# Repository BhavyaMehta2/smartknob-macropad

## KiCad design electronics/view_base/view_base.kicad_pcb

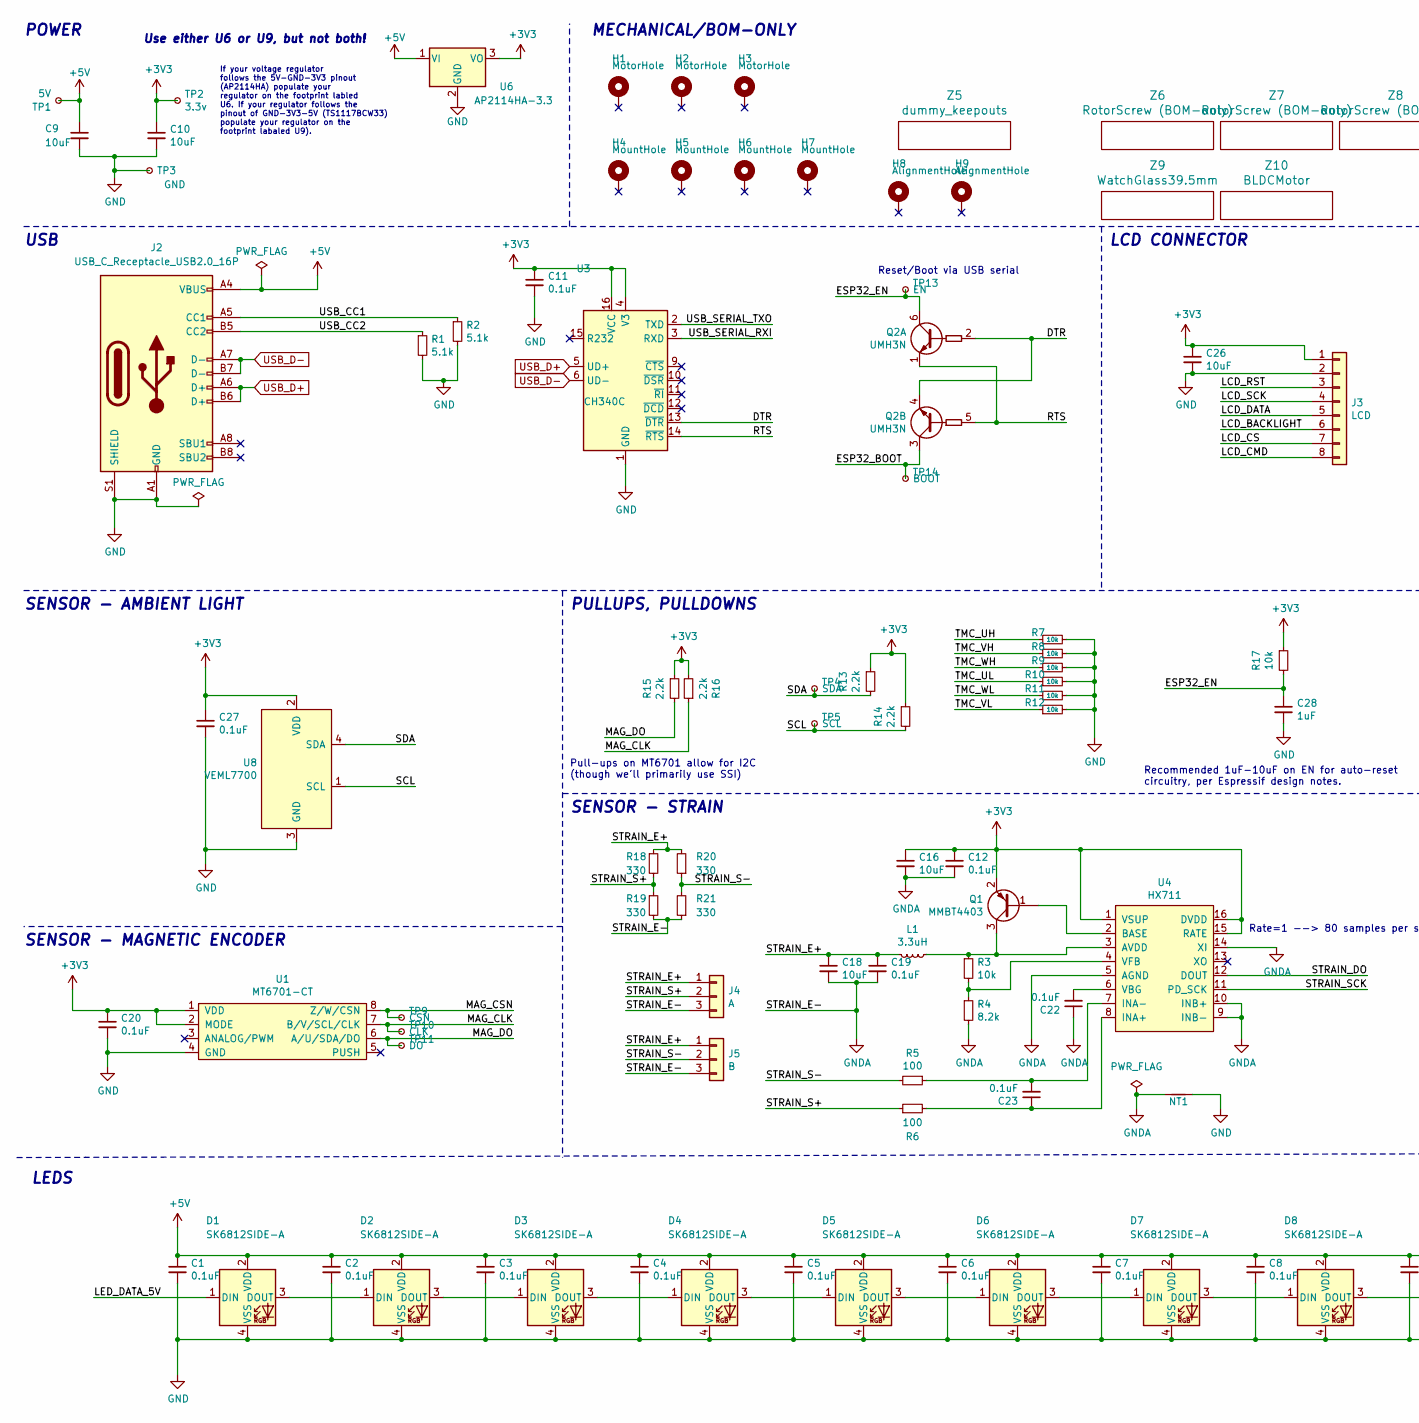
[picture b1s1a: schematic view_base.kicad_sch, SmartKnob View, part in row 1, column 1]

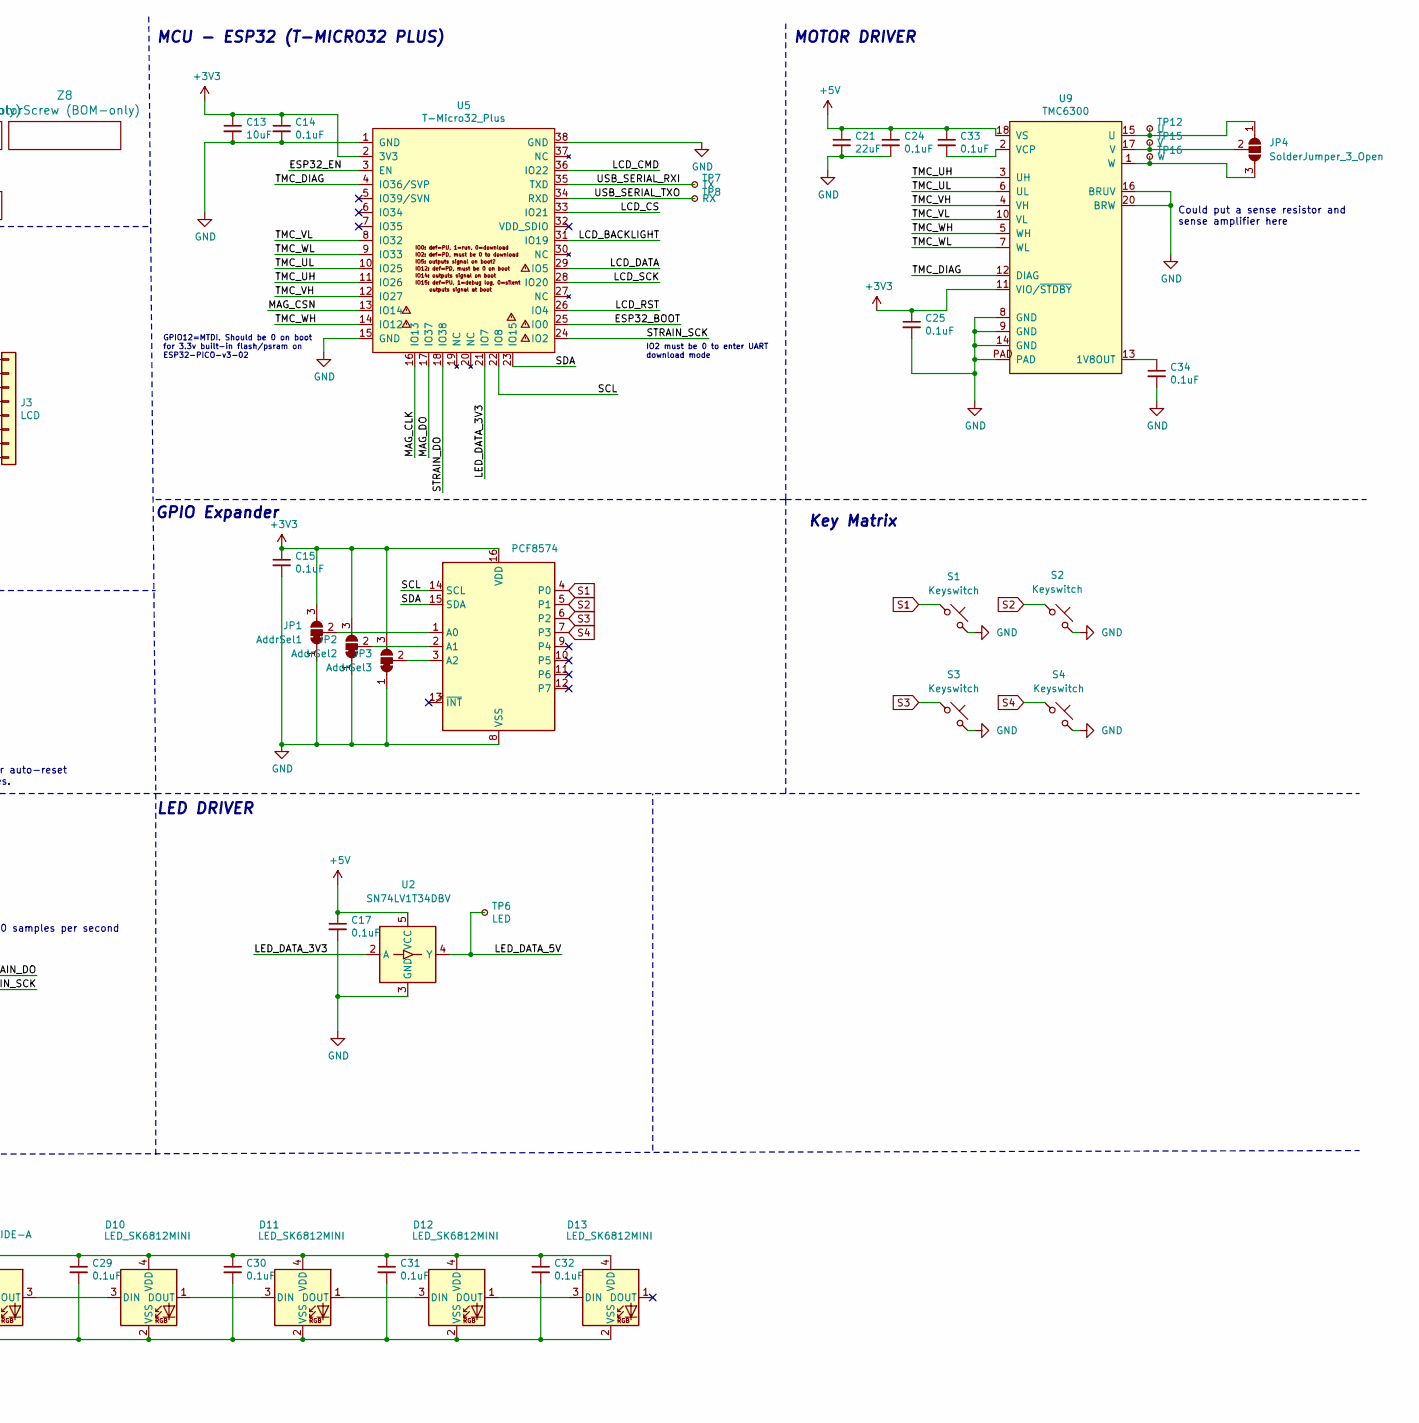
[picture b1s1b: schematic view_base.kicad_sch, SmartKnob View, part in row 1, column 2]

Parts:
C1, C2, C3, C4, C5, C6, C7, C8, C11, C12, C14, C15, C17, C19, C20, C22, C23, C24, C25, C27, C29, C30, C31, C32, C33, C34: 0.1uF; C_0603_1608Metric; LCSC C1591
C9, C10, C13, C16, C18, C26: 10uF; C_0805_2012Metric; LCSC C15850
C21: 22uF; C_0805_2012Metric; LCSC C98190
C28: 1uF; C_0603_1608Metric; Mouser 187-CL10A105KA8NNNC
D1, D2, D3, D4, D5, D6, D7, D8: SK6812SIDE-A; SK6812-SIDE-A; Digikey 1528-4691-ND
D10, D11, D12, D13: LED_SK6812MINI; MX_SK6812MINI-E
H1, H2, H3: MotorHole; MountingHole_M1.6; LCSC C2931389
H4, H5, H6, H7: MountHole; MountingHole_2.2mm_M2_ISO7380_Pad_NonVirtual; LCSC C2911210 or C2911532 (screw), C2961595 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
H8, H9: AlignmentHole; MountingHole_2.2mm_M2_ISO7380_Pad_NonVirtual
J2: USB_C_Receptacle_USB2.0_16P; USB4510_NoPaste
J3: LCD; SolderPads_2mm_8
J4: A; SolderPads_2mm_3_STRAIN
J5: B; SolderPads_2mm_3_STRAIN
JP1: AddrSel1; SolderJumper-3_P1.3mm_Bridged12_Pad1.0x1.5mm_NumberLabels
JP2: AddrSel2; SolderJumper-3_P1.3mm_Bridged12_Pad1.0x1.5mm_NumberLabels
JP3: AddrSel3; SolderJumper-3_P1.3mm_Bridged12_Pad1.0x1.5mm_NumberLabels
JP4: SolderJumper_3_Open; SolderPads_2mm_3
L1: 3.3uH; L_0805_2012Metric; LCSC C307744
NT1: NetTie_2; NetTie-2_SMD_Pad0.5mm
Q1: MMBT4403; SOT-23; LCSC C78864
Q2: UMH3N; SOT-363_SC-70-6; LCSC C62892
R1, R2: 5.1k; R_0603_1608Metric; LCSC C105580
R3, R7, R8, R9, R10, R11, R12, R17: 10k; R_0603_1608Metric; LCSC C98220
R4: 8.2k; R_0603_1608Metric; LCSC C114637
R5, R6: 100; R_0603_1608Metric; LCSC C319953
R13, R14, R15, R16: 2.2k; R_0603_1608Metric; LCSC C4190
R18, R19, R20, R21: 330; R_2512_6332Metric; LCSC C19866
S1, S2, S3, S4: Keyswitch; MX_PCB_1.00u
TP1: 5V; TestPoint_Pad_D2.0mm_ValueSilk
TP2: 3.3v; TestPoint_Pad_D2.0mm_ValueSilk
TP3: GND; TestPoint_Pad_D2.0mm_ValueSilk
TP4: SDA; TestPoint_Pad_D2.0mm_ValueSilk
TP5: SCL; TestPoint_Pad_D2.0mm_ValueSilk
TP6: LED; TestPoint_Pad_D2.0mm_ValueSilk
TP7: TX; TestPoint_Pad_D2.0mm_ValueSilk
TP8: RX; TestPoint_Pad_D2.0mm_ValueSilk
TP9: CSN; TestPoint_Pad_D2.0mm_ValueSilk
TP10: CLK; TestPoint_Pad_D2.0mm_ValueSilk
TP11: DO; TestPoint_Pad_D2.0mm_ValueSilk
TP12: U; TestPoint_Pad_D2.0mm_ValueSilk
TP13: EN; TestPoint_Pad_D2.0mm_ValueSilk
TP14: BOOT; TestPoint_Pad_D2.0mm_ValueSilk
TP15: V; TestPoint_Pad_D2.0mm_ValueSilk
TP16: W; TestPoint_Pad_D2.0mm_ValueSilk
U1: MT6701-CT; SOIC-8_3.9x4.9mm_P1.27mm; LCSC C2856764, or C3003196
U2: SN74LV1T34DBV; SOT-23-5; LCSC C100024
U3: CH340C; SOIC-16_3.9x9.9mm_P1.27mm; LCSC C84681
U4: HX711; SOIC-16_3.9x9.9mm_P1.27mm; LCSC C43656
U5: T-Micro32_Plus; T-Micro32; Digikey N/A
U6: AP2114HA-3.3; SOT-223-3_TabPin2_InGndOut; LCSC C460314
U7: PCF8574; SOP-16_3.9x9.9mm_P1.27mm
U8: VEML7700; VEML7700-TOP; Digikey VEML7700-TT
U9: TMC6300; QFN-20-1EP_3x3mm_P0.4mm_EP1.65x1.65mm_ThermalVias_LargerVia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; Digikey TMC6300-LA-T
Z5: dummy_keepouts; ViewKeepouts3d
Z6, Z7, Z8: RotorScrew (BOM-only); bom_only_no_pin
Z9: WatchGlass39.5mm; bom_only_no_pin
Z10: BLDCMotor; bom_only_no_pin

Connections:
+3V3: C10.1, C11.1, C12.1, C13.1, C14.1, C15.1, C16.1, C20.1, C25.1, C26.1, C27.1, J3.1, JP1.3 (B), JP2.3 (B), JP3.3 (B), Q1.2 (E), R13.1, R14.1, R15.1, R16.2, R17.1, TP2.1, U1.1 (VDD), U1.2 (MODE), U3.4 (V3), U3.16 (VCC), U4.1 (VSUP), U4.15 (RATE), U4.16 (DVDD), U5.2 (3V3), U6.3 (VO), U7.16 (VDD), U8.2 (VDD), U9.11 (VIO/~STDBY)
+5V: C1.1, C2.1, C3.1, C4.1, C5.1, C6.1, C7.1, C8.1, C9.1, C17.1, C21.1, C24.1, C29.1, C30.1, C31.1, C32.1, C33.1, D1.2 (VDD), D2.2 (VDD), D3.2 (VDD), D4.2 (VDD), D5.2 (VDD), D6.2 (VDD), D7.2 (VDD), D8.2 (VDD), D10.4 (VDD), D11.4 (VDD), D12.4 (VDD), D13.4 (VDD), J2.A4 (VBUS), J2.A9 (VBUS), J2.B4 (VBUS), J2.B9 (VBUS), TP1.1, U2.5 (VCC), U6.1 (VI), U9.18 (VS)
/DTR: Q2.2 (B1), Q2.4 (E2), U3.13 (~DTR)
/ESP32_BOOT: Q2.3 (C2), TP14.1, U5.25 (IO0)
/ESP32_EN: C28.1, Q2.6 (C1), R17.2, TP13.1, U5.3 (EN)
/LCD_BACKLIGHT: J3.6, U5.31 (IO19)
/LCD_CMD: J3.8, U5.36 (IO22)
/LCD_CS: J3.7, U5.33 (IO21)
/LCD_DATA: J3.5, U5.29 (IO5)
/LCD_RST: J3.3, U5.26 (IO4)
/LCD_SCK: J3.4, U5.28 (IO20)
/LED_DATA_3V3: U2.2 (A), U5.21 (IO7)
/LED_DATA_5V: D1.1 (DIN), TP6.1, U2.4 (Y)
/MAG_CLK: R16.1, TP10.1, U1.7 (B/V/SCL/CLK), U5.16 (IO13)
/MAG_CSN: TP9.1, U1.8 (Z/W/CSN), U5.13 (IO14)
/MAG_DO: R15.2, TP11.1, U1.6 (A/U/SDA/DO), U5.17 (IO37)
/RTS: Q2.1 (E1), Q2.5 (B2), U3.14 (~RTS)
/SCL: R14.2, TP5.1, U5.22 (IO8), U7.14 (SCL), U8.1 (SCL)
/SDA: R13.2, TP4.1, U5.23 (IO15), U7.15 (SDA), U8.4 (SDA)
/STRAIN_DO: U4.12 (DOUT), U5.18 (IO38)
/STRAIN_E+: C18.1, C19.1, J4.1, J5.1, L1.2, R18.1, R20.2
/STRAIN_S+: J4.2, R6.1, R18.2, R19.1
/STRAIN_S-: J5.2, R5.2, R20.1, R21.2
/STRAIN_SCK: U4.11 (PD_SCK), U5.24 (IO2)
/TMC_DIAG: U5.4 (IO36/SVP), U9.12 (DIAG)
/TMC_UH: R7.1, U5.11 (IO26), U9.3 (UH)
/TMC_UL: R10.1, U5.10 (IO25), U9.6 (UL)
/TMC_VH: R8.1, U5.12 (IO27), U9.4 (VH)
/TMC_VL: R12.1, U5.8 (IO32), U9.10 (VL)
/TMC_WH: R9.1, U5.14 (IO12), U9.5 (WH)
/TMC_WL: R11.1, U5.9 (IO33), U9.7 (WL)
/USB_CC1: J2.A5 (CC1), R2.1
/USB_CC2: J2.B5 (CC2), R1.1
/USB_SERIAL_RXI: TP7.1, U3.3 (RXD), U5.35 (TXD)
/USB_SERIAL_TXO: TP8.1, U3.2 (TXD), U5.34 (RXD)
GND: C1.2, C2.2, C3.2, C4.2, C5.2, C6.2, C7.2, C8.2, C9.2, C10.2, C11.2, C13.2, C14.2, C15.2, C17.2, C20.2, C21.2, C24.2, C25.2, C26.2, C27.2, C28.2, C29.2, C30.2, C31.2, C32.2, C34.2, D1.4 (VSS), D2.4 (VSS), D3.4 (VSS), D4.4 (VSS), D5.4 (VSS), D6.4 (VSS), D7.4 (VSS), D8.4 (VSS), D10.2 (VSS), D11.2 (VSS), D12.2 (VSS), D13.2 (VSS), J2.A1 (GND), J2.A12 (GND), J2.B1 (GND), J2.B12 (GND), J2.S1 (SHIELD), J3.2, JP1.1 (A), JP2.1 (A), JP3.1 (A), NT1.2, R1.2, R2.2, R7.2, R8.2, R9.2, R10.2, R11.2, R12.2, S1.2, S2.2, S3.2, S4.2, TP3.1, U1.4 (GND), U2.3 (GND), U3.1 (GND), U5.1 (GND), U5.15 (GND), U5.38 (GND), U6.2 (GND), U7.8 (VSS), U8.3 (GND), U9.8 (GND), U9.9 (GND), U9.14 (GND), U9.16 (BRUV), U9.20 (BRW), U9.PAD
GNDA: C12.2, C16.2, C18.2, C19.2, C22.1, J4.3, J5.3, NT1.1, R4.2, R19.2, R21.1, U4.5 (AGND), U4.9 (INB-), U4.10 (INB+), U4.14 (XI)
unnamed: D1.3 (DOUT), D2.1 (DIN)
unnamed: D2.3 (DOUT), D3.1 (DIN)
unnamed: D3.3 (DOUT), D4.1 (DIN)
unnamed: D4.3 (DOUT), D5.1 (DIN)
unnamed: D5.3 (DOUT), D6.1 (DIN)
unnamed: D6.3 (DOUT), D7.1 (DIN)
unnamed: D7.3 (DOUT), D8.1 (DIN)
unnamed: D8.3 (DOUT), D10.3 (DIN)
unnamed: D10.1 (DOUT), D11.3 (DIN)
unnamed: D11.1 (DOUT), D12.3 (DIN)
unnamed: D12.1 (DOUT), D13.3 (DIN)
unnamed: JP1.2 (C), U7.1 (A0)
unnamed: JP2.2 (C), U7.2 (A1)
unnamed: JP3.2 (C), U7.3 (A2)
unnamed: JP4.1 (A), TP12.1, U9.15 (U)
unnamed: JP4.3 (B), TP16.1, U9.1 (W)
unnamed: JP4.2 (C), TP15.1, U9.17 (V)
unnamed: Q1.1 (B), U4.2 (BASE)
unnamed: L1.1, Q1.3 (C), R3.1, U4.3 (AVDD)
unnamed: C23.1, R6.2, U4.8 (INA+)
unnamed: C23.2, R5.1, U4.7 (INA-)
unnamed: C22.2, U4.6 (VBG)
unnamed: R3.2, R4.1, U4.4 (VFB)
unnamed: C34.1, U9.13 (1V8OUT)
unnamed: C33.2, U9.2 (VCP)
S1: S1.1, U7.4 (P0)
S2: S2.1, U7.5 (P1)
S3: S3.1, U7.6 (P2)
S4: S4.1, U7.7 (P3)
USB_D+: J2.A6 (D+), J2.B6 (D+), U3.5 (UD+)
USB_D-: J2.A7 (D-), J2.B7 (D-), U3.6 (UD-)

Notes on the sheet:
POWER
If your voltage regulator follows the 5V-GND-3V3 pinout (AP2114HA) populate your regulator on the footprint labled U6. If your regulator follows the pinout of GND-3V3-5V (TS1117BCW33) populate your regulator on the footprint labaled U9).
SENSOR - MAGNETIC ENCODER
Could put a sense resistor and sense amplifier here
MECHANICAL/BOM-ONLY
Pull-ups on MT6701 allow for I2C (though we'll primarily use SSI)
Use either U6 or U9, but not both!
Rate=1 --> 80 samples per second
GPIO12=MTDI. Should be 0 on boot for 3.3v built-in flash/psram on ESP32-PICO-v3-02
LEDS
SENSOR - AMBIENT LIGHT
GPIO Expander
Recommended 1uF-10uF on EN for auto-reset circuitry, per Espressif design notes.
MCU - ESP32 (T-MICRO32 PLUS)
USB
SENSOR - STRAIN
MOTOR DRIVER
Key Matrix
IO2 must be 0 to enter UART download mode
PULLUPS, PULLDOWNS
LED DRIVER
LCD CONNECTOR
Reset/Boot via USB serial

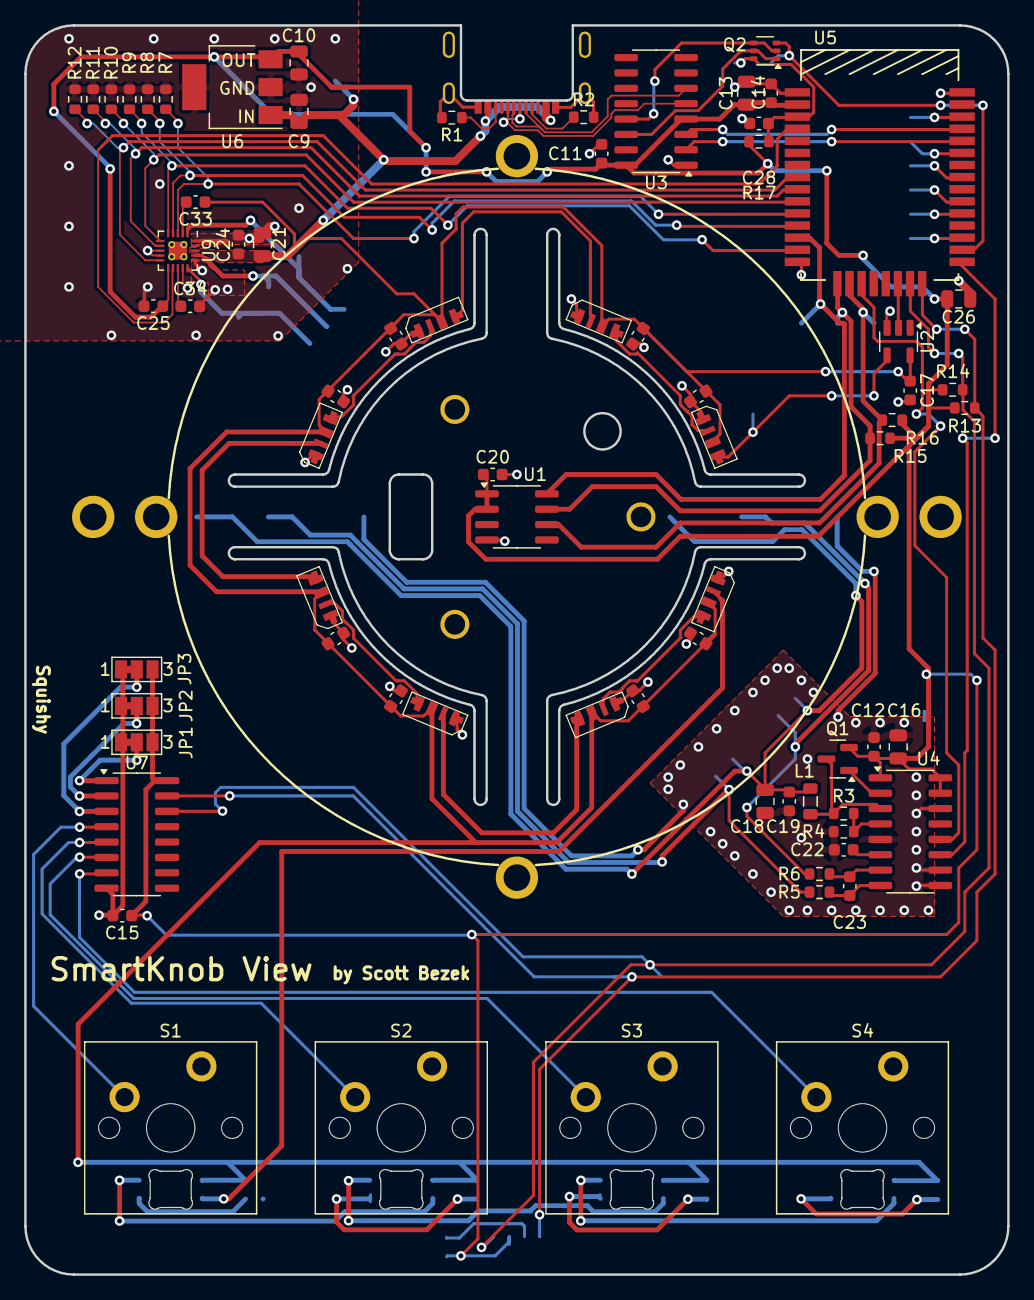
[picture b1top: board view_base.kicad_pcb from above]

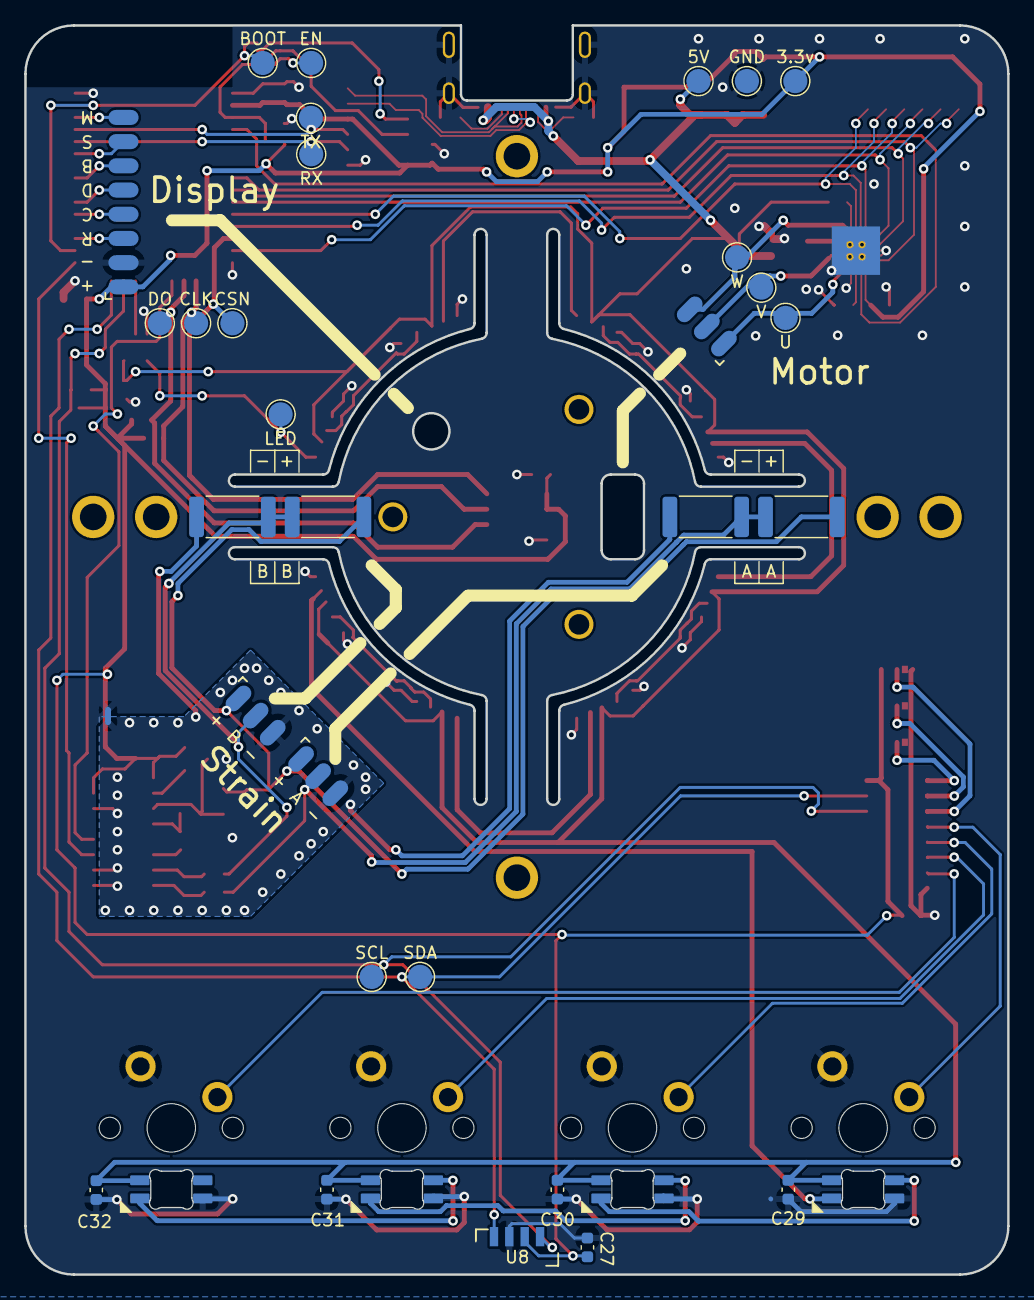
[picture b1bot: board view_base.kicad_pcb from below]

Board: 2 copper layers, 81.2 x 103.2 mm, 123 parts (31 on the bottom side), 68 nets.

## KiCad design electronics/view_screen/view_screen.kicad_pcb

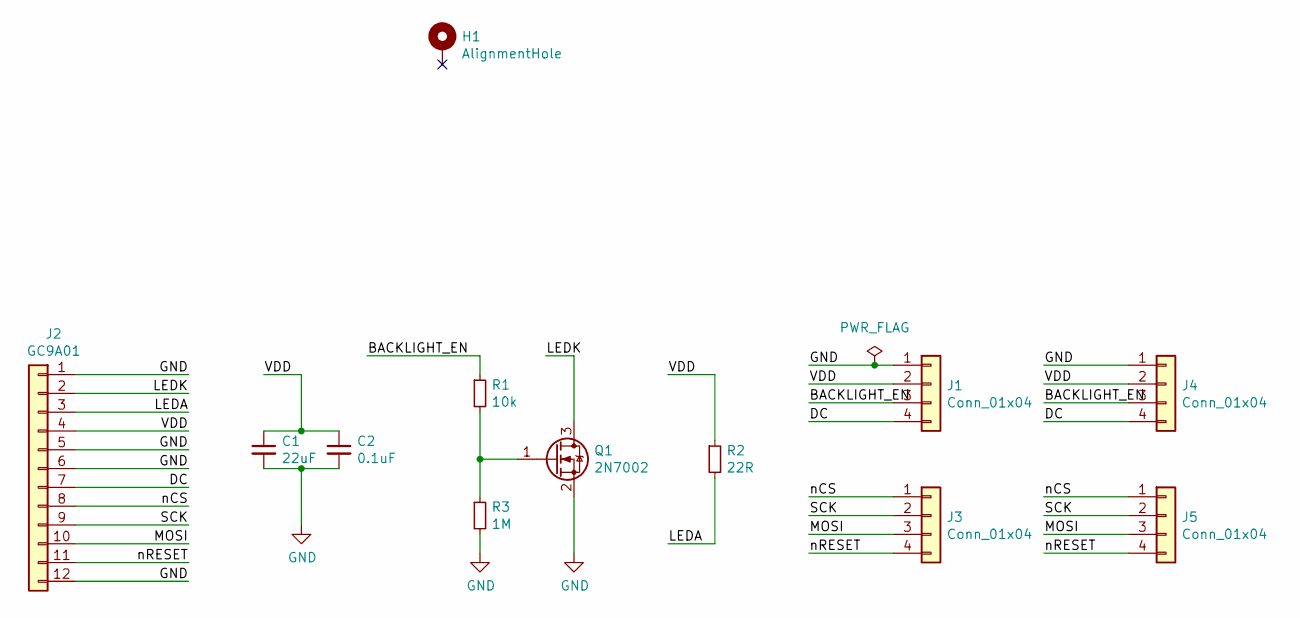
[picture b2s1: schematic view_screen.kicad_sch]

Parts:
C1: 22uF; C_0805_2012Metric; Digikey 1276-CL21A226MAYNNNECT-ND
C2: 0.1uF; C_0603_1608Metric; Digikey 1276-1935-1-ND
H1: AlignmentHole; AlignmentHole_1.6
J1, J3, J4, J5: Conn_01x04; SolderPads_2mm_4
J2: GC9A01; GC9A01Round1.28; Digikey N/A
Q1: 2N7002; SOT-23; Digikey 2N7002H6327XTSA2CT-ND
R1: 10k; R_0603_1608Metric; Digikey RMCF0603JT10K0CT-ND
R2: 22R; R_0603_1608Metric; Digikey RMCF0603JT22R0CT-ND
R3: 1M; R_0603_1608Metric; Digikey RMCF0603JT1M00CT-ND

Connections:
/BACKLIGHT_EN: J1.3, J4.3, R1.1
/DC: J1.4, J2.7, J4.4
/LEDA: J2.3, R2.2
/LEDK: J2.2, Q1.3 (D)
/MOSI: J2.10, J3.3, J5.3
/SCK: J2.9, J3.2, J5.2
/VDD: C1.1, C2.1, J1.2, J2.4, J4.2, R2.1
/nCS: J2.8, J3.1, J5.1
/nRESET: J2.11, J3.4, J5.4
GND: C1.2, C2.2, J1.1, J2.1, J2.5, J2.6, J2.12, J4.1, Q1.2 (S), R3.2
unnamed: Q1.1 (G), R1.2, R3.1

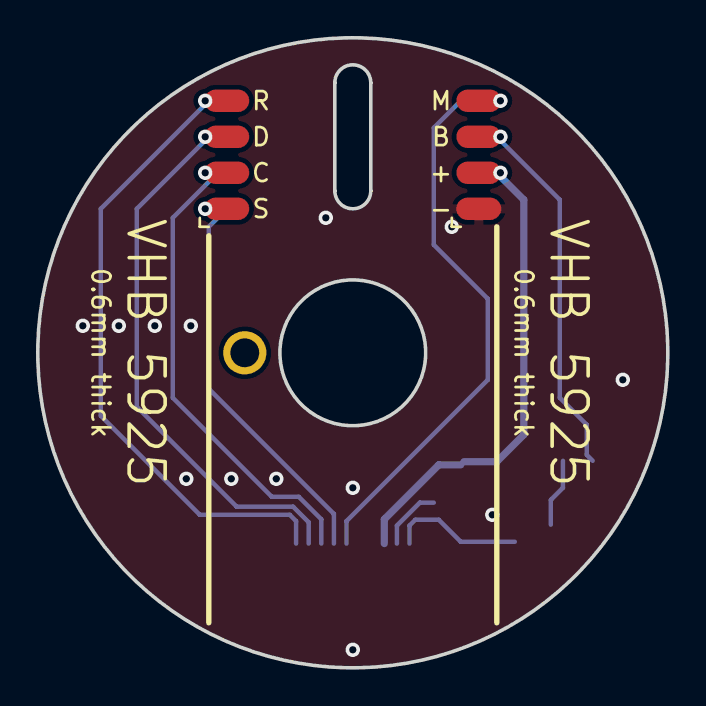
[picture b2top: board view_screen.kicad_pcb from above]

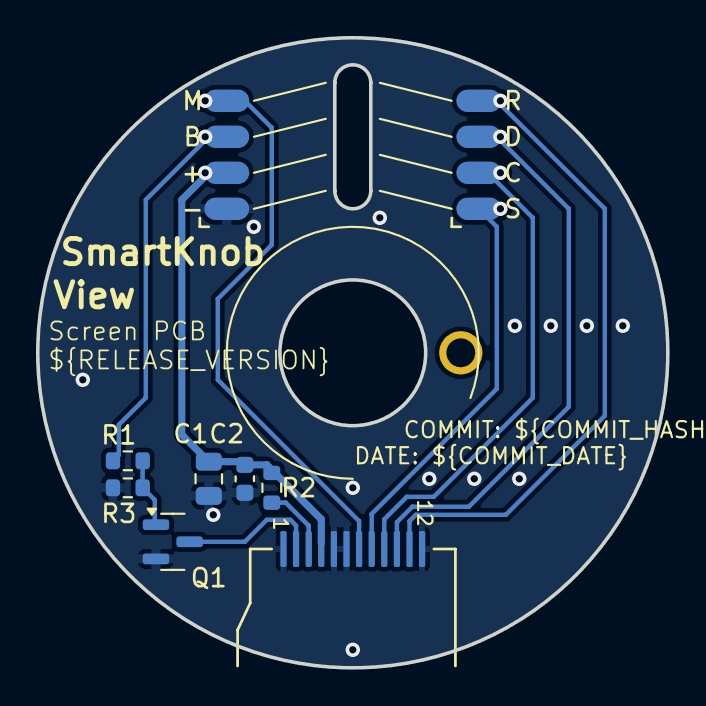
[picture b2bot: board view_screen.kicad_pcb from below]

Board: 2 copper layers, 35.0 x 35.0 mm, 12 parts (9 on the bottom side), 11 nets.

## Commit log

2024-10-20 init
